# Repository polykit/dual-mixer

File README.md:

# Polykit Simple Dual Mixer

Simple dual mixer schematics and PCB based on two TL072 op-amps. It got 8 inputs, a normal and an inverted output on each mixer.

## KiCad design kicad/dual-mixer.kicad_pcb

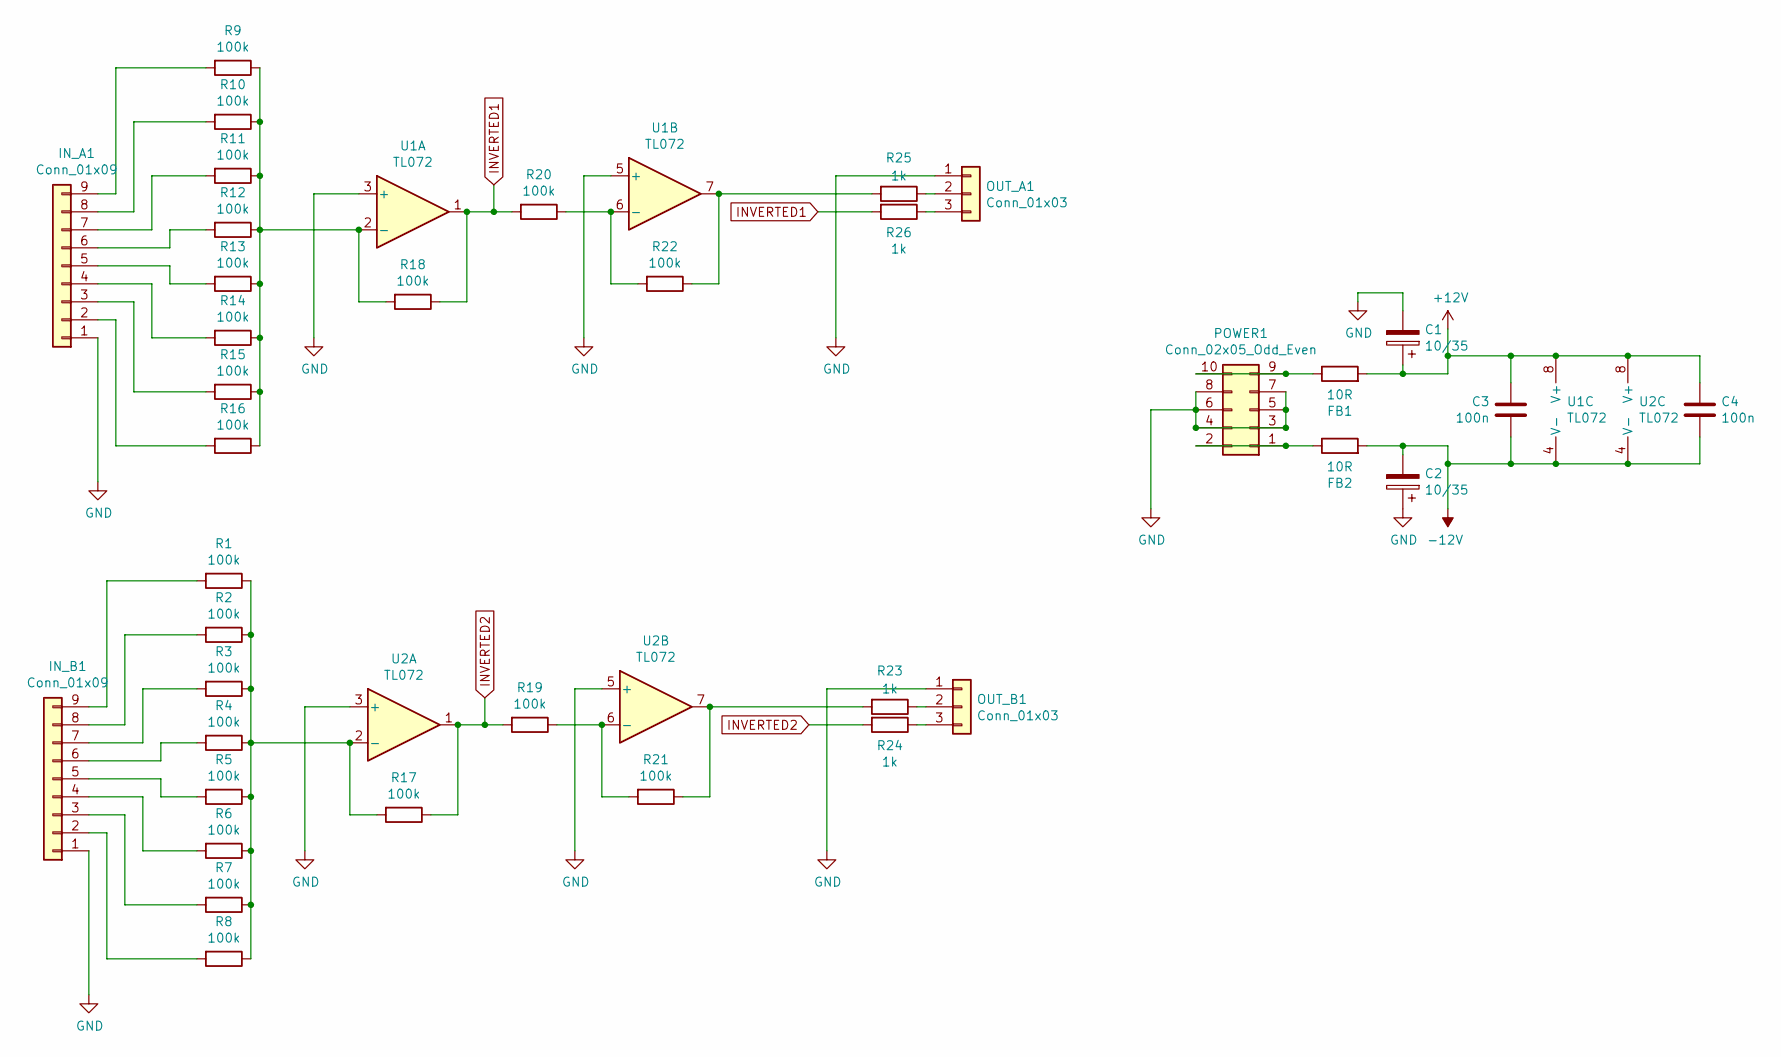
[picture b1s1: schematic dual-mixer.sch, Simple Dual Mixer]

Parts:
C1, C2: 10/35; CP_Radial_D5.0mm_P2.50mm
C3, C4: 100n; C_Rect_L7.0mm_W2.5mm_P5.00mm
FB1, FB2: 10R; R_Axial_DIN0207_L6.3mm_D2.5mm_P10.16mm_Horizontal
IN_A1: Conn_01x09; PinHeader_1x09_P2.54mm_Vertical
IN_B1: Conn_01x09; PinHeader_1x09_P2.54mm_Vertical
OUT_A1: Conn_01x03; PinHeader_1x03_P2.54mm_Vertical
OUT_B1: Conn_01x03; PinHeader_1x03_P2.54mm_Vertical
POWER1: Conn_02x05_Odd_Even; IDC-Header_2x05_P2.54mm_Vertical
R1, R2, R3, R4, R5, R6, R7, R8, R9, R10, R11, R12, R13, R14, R15, R16, R17, R18, R19, R20, R21, R22: 100k; R_Axial_DIN0207_L6.3mm_D2.5mm_P10.16mm_Horizontal
R23, R24, R25, R26: 1k; R_Axial_DIN0207_L6.3mm_D2.5mm_P10.16mm_Horizontal
U1, U2: TL072; DIP-8_W7.62mm_LongPads

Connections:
+12V: C1.1, C3.1, C4.1, FB1.2, U1.8 (V+), U2.8 (V+)
-12V: C2.2, C3.2, C4.2, FB2.2, U1.4 (V-), U2.4 (V-)
GND: C1.2, C2.1, IN_A1.1, IN_B1.1, OUT_A1.1, OUT_B1.1, POWER1.3, POWER1.4, POWER1.5, POWER1.6, POWER1.7, POWER1.8, U1.3 (+), U1.5 (+), U2.3 (+), U2.5 (+)
INVERTED1: R18.1, R20.2, R26.2, U1.1
INVERTED2: R17.1, R19.2, R24.2, U2.1
unnamed: FB1.1, POWER1.9, POWER1.10
unnamed: FB2.1, POWER1.1, POWER1.2
unnamed: IN_A1.2, R16.2
unnamed: IN_A1.3, R15.2
unnamed: IN_A1.4, R14.2
unnamed: IN_A1.5, R13.2
unnamed: IN_A1.6, R12.2
unnamed: IN_A1.7, R11.2
unnamed: IN_A1.8, R10.2
unnamed: IN_A1.9, R9.2
unnamed: IN_B1.2, R8.2
unnamed: IN_B1.3, R7.2
unnamed: IN_B1.4, R6.2
unnamed: IN_B1.5, R5.2
unnamed: IN_B1.6, R4.2
unnamed: IN_B1.7, R3.2
unnamed: IN_B1.8, R2.2
unnamed: IN_B1.9, R1.2
unnamed: OUT_A1.2, R25.1
unnamed: OUT_A1.3, R26.1
unnamed: OUT_B1.2, R23.1
unnamed: OUT_B1.3, R24.1
unnamed: R1.1, R2.1, R3.1, R4.1, R5.1, R6.1, R7.1, R8.1, R17.2, U2.2 (-)
unnamed: R9.1, R10.1, R11.1, R12.1, R13.1, R14.1, R15.1, R16.1, R18.2, U1.2 (-)
unnamed: R19.1, R21.2, U2.6 (-)
unnamed: R20.1, R22.2, U1.6 (-)
unnamed: R21.1, R23.2, U2.7
unnamed: R22.1, R25.2, U1.7

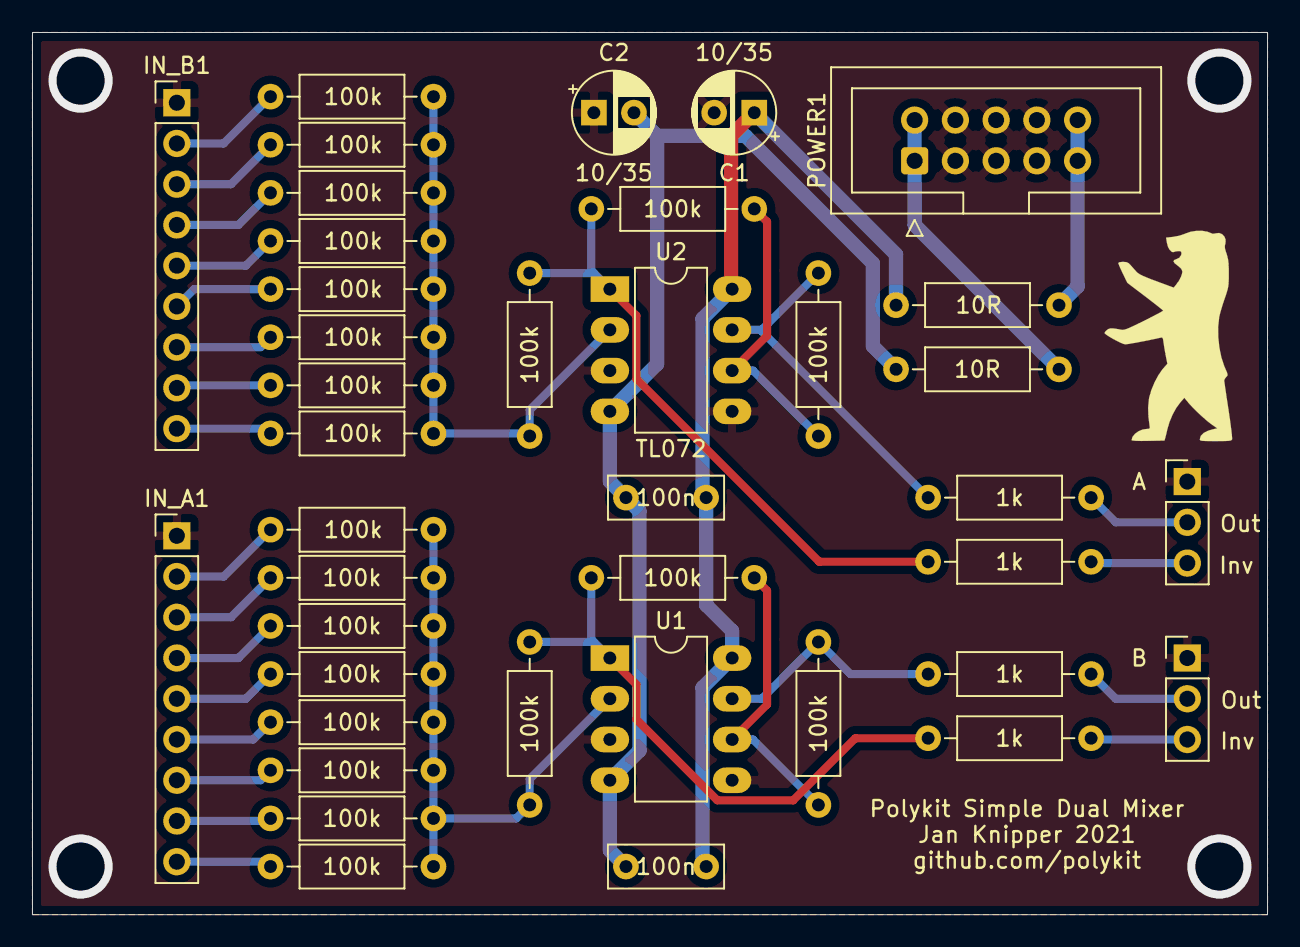
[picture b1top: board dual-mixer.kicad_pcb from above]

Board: 2 copper layers, 77.0 x 55.0 mm, 39 parts (0 on the bottom side), 33 nets.

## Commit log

2021-01-19 Initial import
